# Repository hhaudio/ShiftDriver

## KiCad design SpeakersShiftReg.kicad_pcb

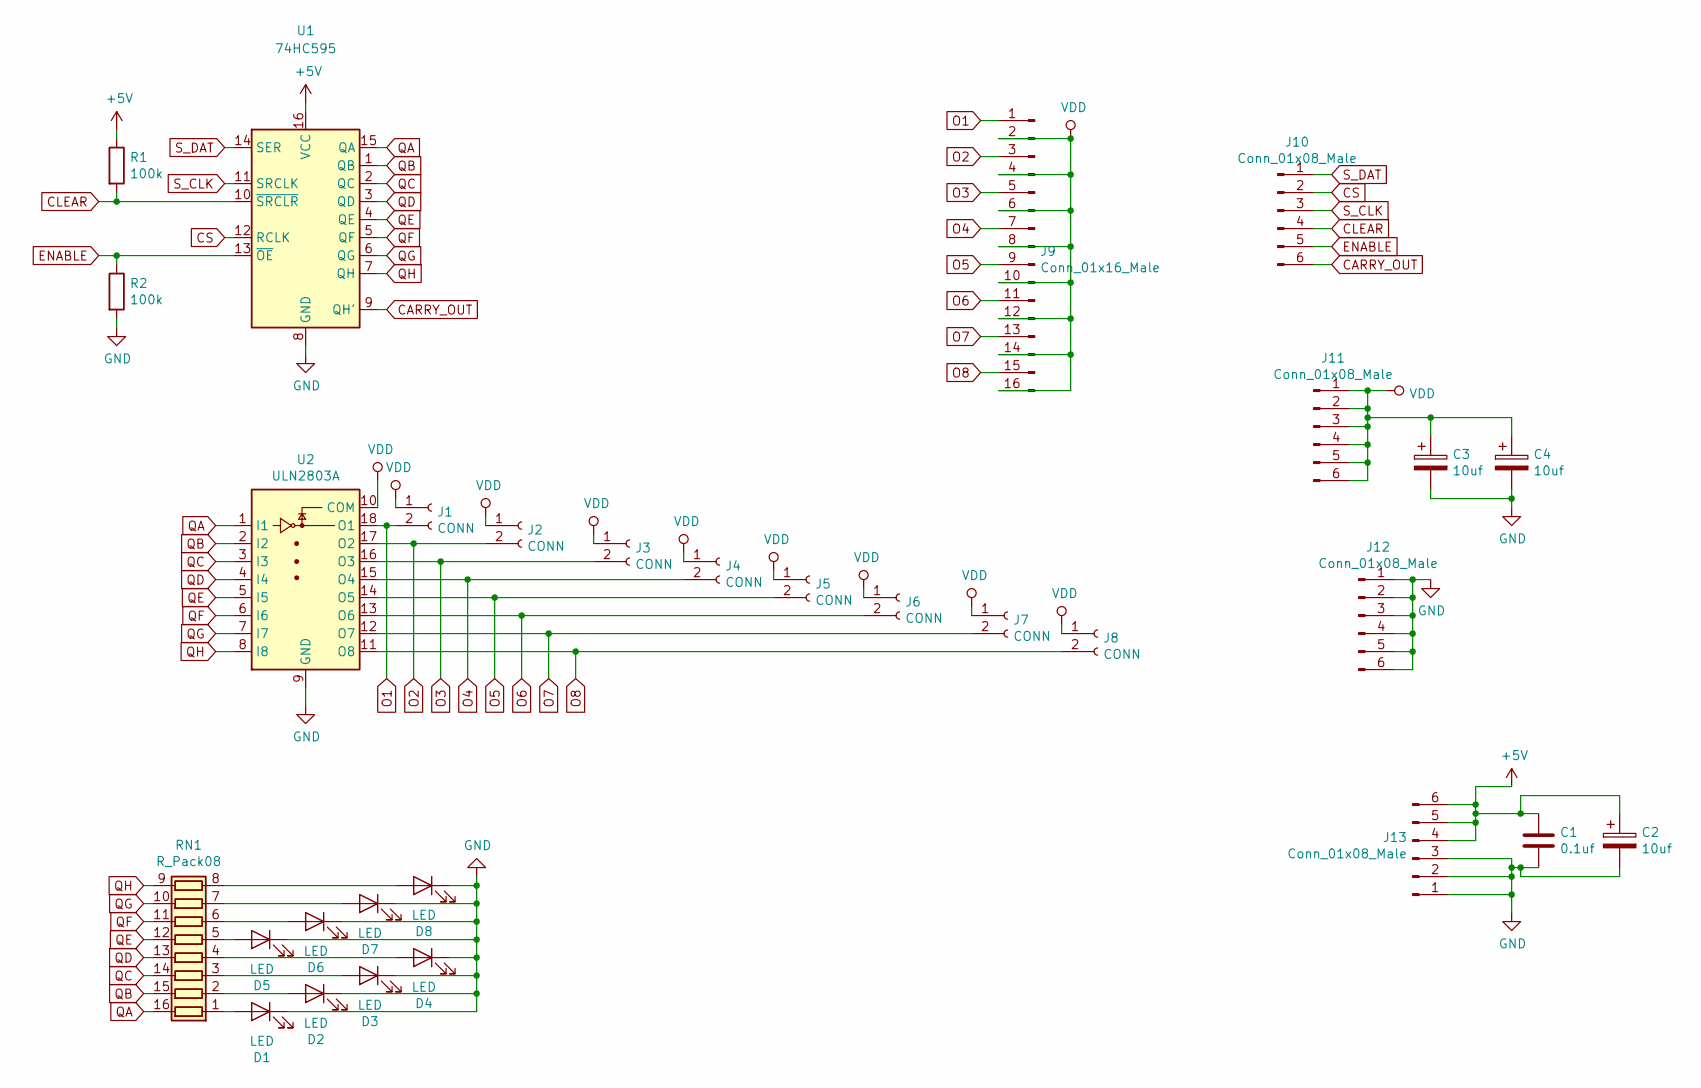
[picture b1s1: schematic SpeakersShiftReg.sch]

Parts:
C1: 0.1uf; C_Disc_D3.0mm_W2.0mm_P2.50mm
C2, C3, C4: 10uf; CP_Radial_D5.0mm_P2.00mm
D1, D2, D3, D4, D5, D6, D7, D8: LED; LED_D5.0mm
J1, J2, J3, J4, J5, J6, J7, J8: CONN; Phoenix_Stacked
J9: Conn_01x16_Male; PinHeader_2x08_P2.54mm_Vertical
J10, J11, J12, J13: Conn_01x08_Male; PinSocket_1x08_P2.54mm_Vertical
R1, R2: 100k; R_THT_P7.62
RN1: R_Pack08; DIP-16_W7.62mm_Socket
U1: 74HC595; DIP-16_W7.62mm_Socket
U2: ULN2803A; DIP-18_W7.62mm_Socket

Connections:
+5V: C1.1, C2.1, J13.4, J13.5, J13.6, R1.1, U1.16 (VCC)
CARRY_OUT: J10.6, U1.9 (QH')
CLEAR: J10.4, R1.2, U1.10 (~SRCLR)
CS: J10.2, U1.12 (RCLK)
ENABLE: J10.5, R2.1, U1.13 (~OE)
GND: C1.2, C2.2, C3.2, C4.2, D1.1 (K), D2.1 (K), D3.1 (K), D4.1 (K), D5.1 (K), D6.1 (K), D7.1 (K), D8.1 (K), J12.1, J12.2, J12.3, J12.4, J12.5, J12.6, J13.1, J13.2, J13.3, R2.2, U1.8 (GND), U2.9 (GND)
unnamed: D1.2 (A), RN1.1 (R1.1)
unnamed: D2.2 (A), RN1.2 (R2.1)
unnamed: D3.2 (A), RN1.3 (R3.1)
unnamed: D4.2 (A), RN1.4 (R4.1)
unnamed: D5.2 (A), RN1.5 (R5.1)
unnamed: D6.2 (A), RN1.6 (R6.1)
unnamed: D7.2 (A), RN1.7 (R7.1)
unnamed: D8.2 (A), RN1.8 (R8.1)
O1: J1.2, J9.1, U2.18 (O1)
O2: J2.2, J9.3, U2.17 (O2)
O3: J3.2, J9.5, U2.16 (O3)
O4: J4.2, J9.7, U2.15 (O4)
O5: J5.2, J9.9, U2.14 (O5)
O6: J6.2, J9.11, U2.13 (O6)
O7: J7.2, J9.13, U2.12 (O7)
O8: J8.2, J9.15, U2.11 (O8)
QA: RN1.16 (R1.2), U1.15 (QA), U2.1 (I1)
QB: RN1.15 (R2.2), U1.1 (QB), U2.2 (I2)
QC: RN1.14 (R3.2), U1.2 (QC), U2.3 (I3)
QD: RN1.13 (R4.2), U1.3 (QD), U2.4 (I4)
QE: RN1.12 (R5.2), U1.4 (QE), U2.5 (I5)
QF: RN1.11 (R6.2), U1.5 (QF), U2.6 (I6)
QG: RN1.10 (R7.2), U1.6 (QG), U2.7 (I7)
QH: RN1.9 (R8.2), U1.7 (QH), U2.8 (I8)
S_CLK: J10.3, U1.11 (SRCLK)
S_DAT: J10.1, U1.14 (SER)
VDD: C3.1, C4.1, J1.1, J2.1, J3.1, J4.1, J5.1, J6.1, J7.1, J8.1, J9.2, J9.4, J9.6, J9.8, J9.10, J9.12, J9.14, J9.16, J11.1, J11.2, J11.3, J11.4, J11.5, J11.6, U2.10 (COM)

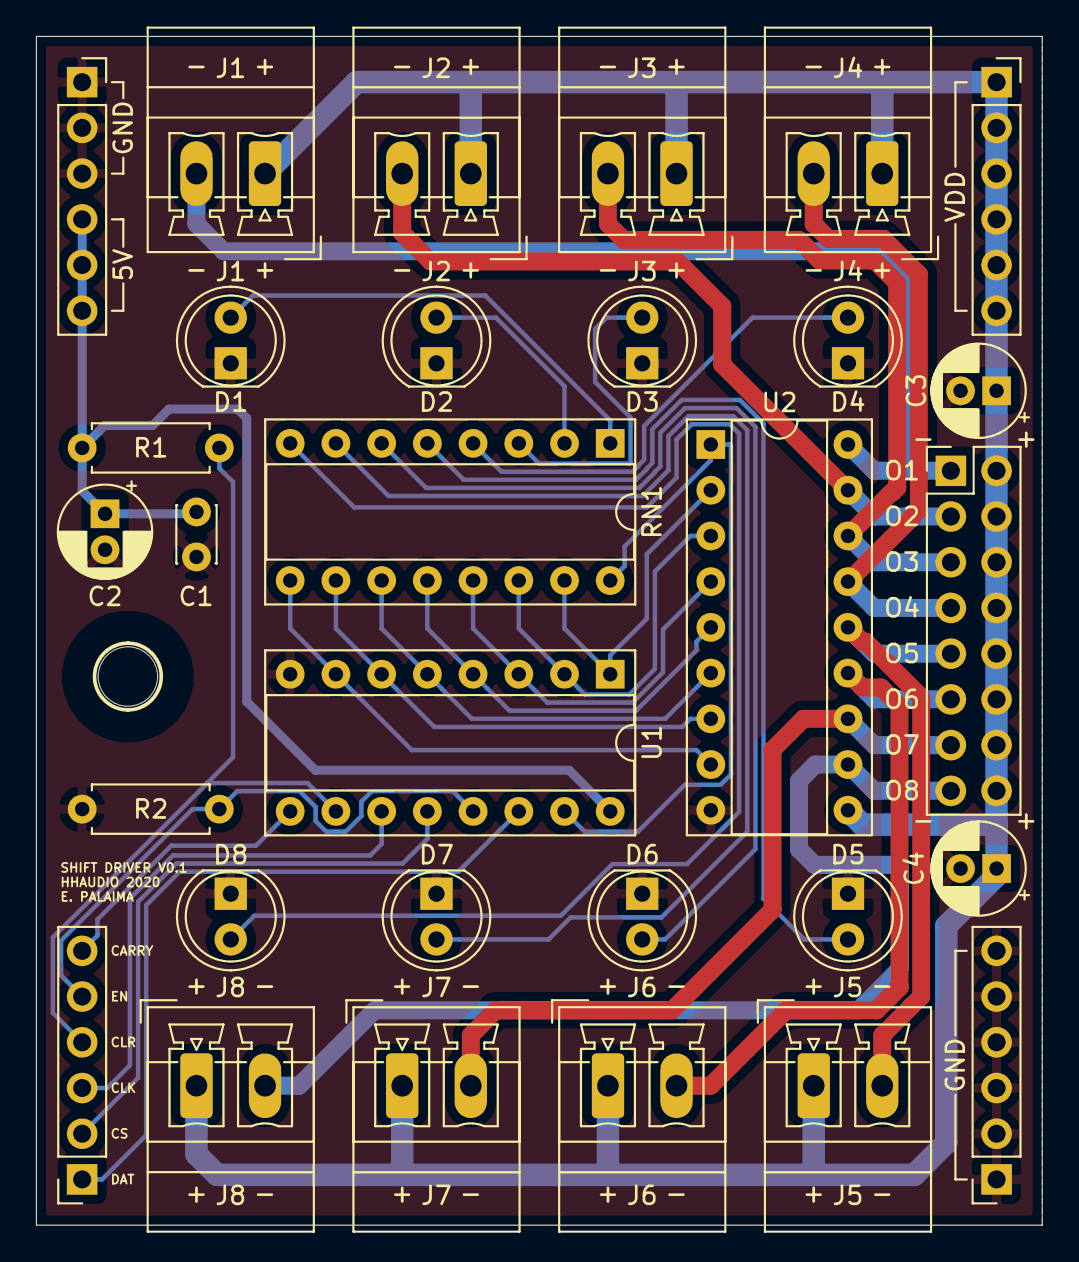
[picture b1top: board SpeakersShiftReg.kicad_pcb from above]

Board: 2 copper layers, 55.9 x 66.0 mm, 32 parts (1 on the bottom side), 33 nets.

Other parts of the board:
H3: M3/#4-40; M3_MOUNT
HHLogo_11.5mm: Val**; HHLOGO_11mm

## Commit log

2020-05-17 determined rough form for PCB
2020-05-17 added silk, ready for traces
2020-05-17 commit before trying thing
2020-05-17 finish layout
2020-05-18 finished layout
2020-05-19 commit before changing output polarity
